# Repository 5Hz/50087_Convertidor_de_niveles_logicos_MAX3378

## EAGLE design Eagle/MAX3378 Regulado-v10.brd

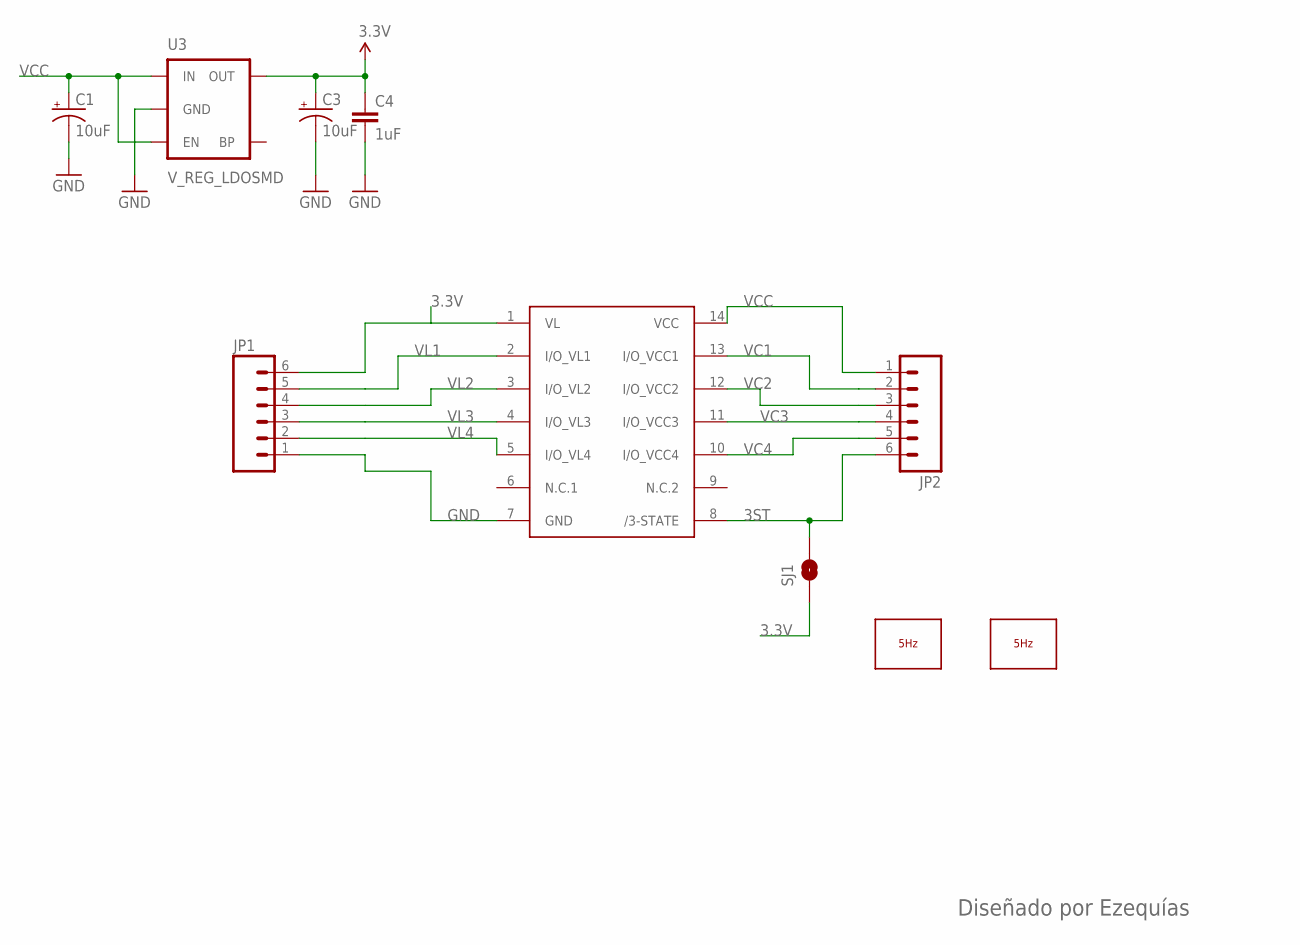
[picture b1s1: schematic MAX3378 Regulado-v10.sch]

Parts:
C1, C3: 10uF; EIA3216
C4: 1uF; 0603-CAP
JP1, JP2: M06SIP; 1X06
LOGO1: LOGO_5HZ_H_COOPER_15MM; 5HZ_LOGO_H_COOPER_15MM
LOGO2: LOGO_5HZ_WEB_10MM; 5HZ_WEB_10MM
SJ1: SOLDERJUMPERNO; SJ_2S-NO
U3: V_REG_LDOSMD; SOT23-5
U$1: MAX3378; TSSOP14

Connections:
3.3V: C3.A (+), C4.1, JP1.6, SJ1.1, U3.5 (OUT), U$1.1 (VL)
3ST: JP2.6, SJ1.2, U$1.8 (/3-STATE)
GND: C1.C (-), C3.C (-), C4.2, JP1.1, U3.2 (GND), U$1.7 (GND)
VC1: JP2.2, U$1.13 (I/O_VCC1)
VC2: JP2.3, U$1.12 (I/O_VCC2)
VC3: JP2.4, U$1.11 (I/O_VCC3)
VC4: JP2.5, U$1.10 (I/O_VCC4)
VCC: C1.A (+), JP2.1, U3.1 (IN), U3.3 (EN), U$1.14 (VCC)
VL1: JP1.5, U$1.2 (I/O_VL1)
VL2: JP1.4, U$1.3 (I/O_VL2)
VL3: JP1.3, U$1.4 (I/O_VL3)
VL4: JP1.2, U$1.5 (I/O_VL4)

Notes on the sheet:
Diseñado por Ezequías

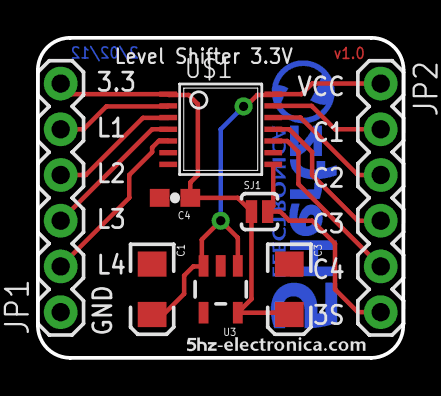
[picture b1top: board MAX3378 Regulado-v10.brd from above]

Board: 2 copper layers, 20.3 x 17.8 mm, 10 parts (1 on the bottom side), 12 nets.

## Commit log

2014-01-13 creación
